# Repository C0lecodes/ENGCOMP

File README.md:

# PillPath — Dispenser Demonstration

PillPath is a local demonstration portal for the UC Engineering Challenge. It manages a small fleet of ESP32 pill dispensers, provides a care-team dashboard, maintains a dose history, alerts when a dose remains **undispensed** for 30 minutes, and alerts when medication stock reaches its refill threshold.

## Run the Portal

Requires Python 3.10+ and uses only the Python standard library.

From the project directory, run:

```sh
python3 server.py
```

Then open:

```text
http://localhost:3000
```

Press **Reset demo** to return to the initial demonstration data.

To demonstrate a missed-dose alert, add a dose with a scheduled time more than 30 minutes in the past.

## Demonstrate with an ESP32

### 1. Open the project

Open the project folder in VS Code and install the **PlatformIO IDE** extension if it is not already installed.

### 2. Configure the ESP32

Open:

```text
src/main.cpp
```

Set the Wi-Fi credentials for your network.

Then change `SERVER_URL` to the IP address of the computer running the PillPath server. For example:

```cpp
#define SERVER_URL "http://192.156.1.100:3000"
```

The computer and ESP32 must be connected to the same local network.

### 3. Connect and upload

Attach a momentary button between **GPIO 18** and **GND**.

In PlatformIO:

1. Select **Upload** to upload the firmware.
2. Select **Monitor** to open the serial monitor.
3. Press the button to trigger a demonstration dispense.

### 4. Demonstration mode

`DEMO_WITHOUT_MOTORS` is set to `true` by default.

This allows the ESP32 to be demonstrated without motor hardware connected. When the button is pressed, the ESP32:

1. Requests the next pending dose.
2. Simulates the dispensing cycle.
3. Records the dispense with the PillPath server.
4. Decreases the medication stock.

## Hardware Mapping and Safety

The PlatformIO firmware reserves the following GPIO pins for the motor drivers:

| GPIO    | Function               |
| ------- | ---------------------- |
| GPIO 26 | Top barrel step        |
| GPIO 27 | Top barrel direction   |
| GPIO 32 | Lower barrel step      |
| GPIO 33 | Lower barrel direction |

Set:

```cpp
DEMO_WITHOUT_MOTORS
```

to `false` only after the motor hardware has been connected and the `stepMotor` counts have been calibrated for the final mechanical gearing.

For a physical prototype, add appropriate end stops and/or jam detection before operating the mechanism unattended.

### Important limitation

PillPath records a **device dispensing action**. It does not verify that a person actually received or swallowed a medication.

This project is a demonstration prototype and must not be used for clinical decisions or real medication management without appropriate security, authentication, encrypted communication, audit controls, privacy review, and validated hardware and sensors.

## API Endpoints

### `POST /api/device/heartbeat`

Updates the connection status of an ESP32 dispenser.

### `POST /api/device/dispense`

Records a pending dose as dispensed and decreases the corresponding medication stock.

### `GET /api/dashboard`

Returns dashboard data and evaluates the current alerts.

## Data Storage

Persistent demonstration data is stored in:

```text
data.json
```

The file is created automatically when the server first saves data.

## Project Structure

A typical project structure is:

```text
PillPath/
├── server.py
├── data.json
├── src/
│   └── main.cpp
└── ...
```

`data.json` is generated automatically and does not need to be created manually.

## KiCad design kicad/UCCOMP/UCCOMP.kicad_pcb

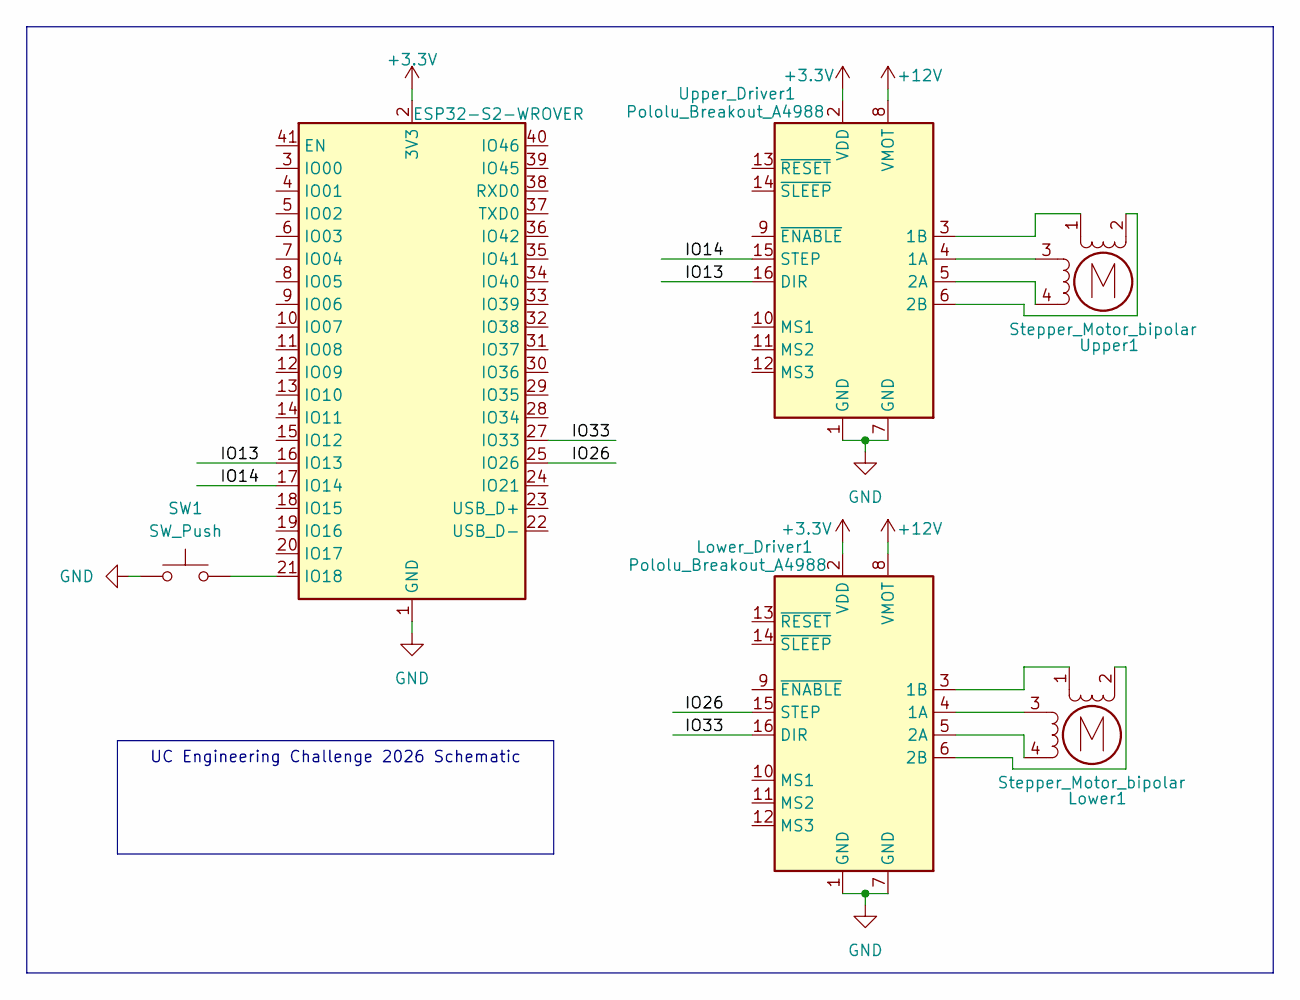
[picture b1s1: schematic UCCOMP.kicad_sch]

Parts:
Lower1: Stepper_Motor_bipolar; TerminalBlock_Phoenix_MKDS-1,5-4-5.08_1x04_P5.08mm_Horizont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
Lower_Driver1: Pololu_Breakout_A4988; Pololu_Breakout-16_15.2x20.3mm
SW1: SW_Push; SW_PUSH-12mm
U1: ESP32-S2-WROVER
Upper1: Stepper_Motor_bipolar; TerminalBlock_Phoenix_MKDS-1,5-4-5.08_1x04_P5.08mm_Horizont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
Upper_Driver1: Pololu_Breakout_A4988; Pololu_Breakout-16_15.2x20.3mm

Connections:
+3.3V: Lower_Driver1.2 (VDD), U1.2 (3V3), Upper_Driver1.2 (VDD)
+12V: Lower_Driver1.8 (VMOT), Upper_Driver1.8 (VMOT)
/IO13: U1.16 (IO13), Upper_Driver1.16 (DIR)
/IO14: U1.17 (IO14), Upper_Driver1.15 (STEP)
/IO26: Lower_Driver1.15 (STEP), U1.25 (IO26)
/IO33: Lower_Driver1.16 (DIR), U1.27 (IO33)
GND: Lower_Driver1.1 (GND), Lower_Driver1.7 (GND), SW1.1, U1.1 (GND), U1.26 (GND), U1.42 (GND), U1.43 (GND), Upper_Driver1.1 (GND), Upper_Driver1.7 (GND)
unnamed: Lower1.2 (-), Lower_Driver1.6 (2B)
unnamed: Lower1.3, Lower_Driver1.4 (1A)
unnamed: Lower1.1, Lower_Driver1.3 (1B)
unnamed: Lower1.4, Lower_Driver1.5 (2A)
unnamed: SW1.2, U1.21 (IO18)
unnamed: Upper1.2 (-), Upper_Driver1.6 (2B)
unnamed: Upper1.3, Upper_Driver1.4 (1A)
unnamed: Upper1.1, Upper_Driver1.3 (1B)
unnamed: Upper1.4, Upper_Driver1.5 (2A)

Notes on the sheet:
UC Engineering Challenge 2026 Schematic

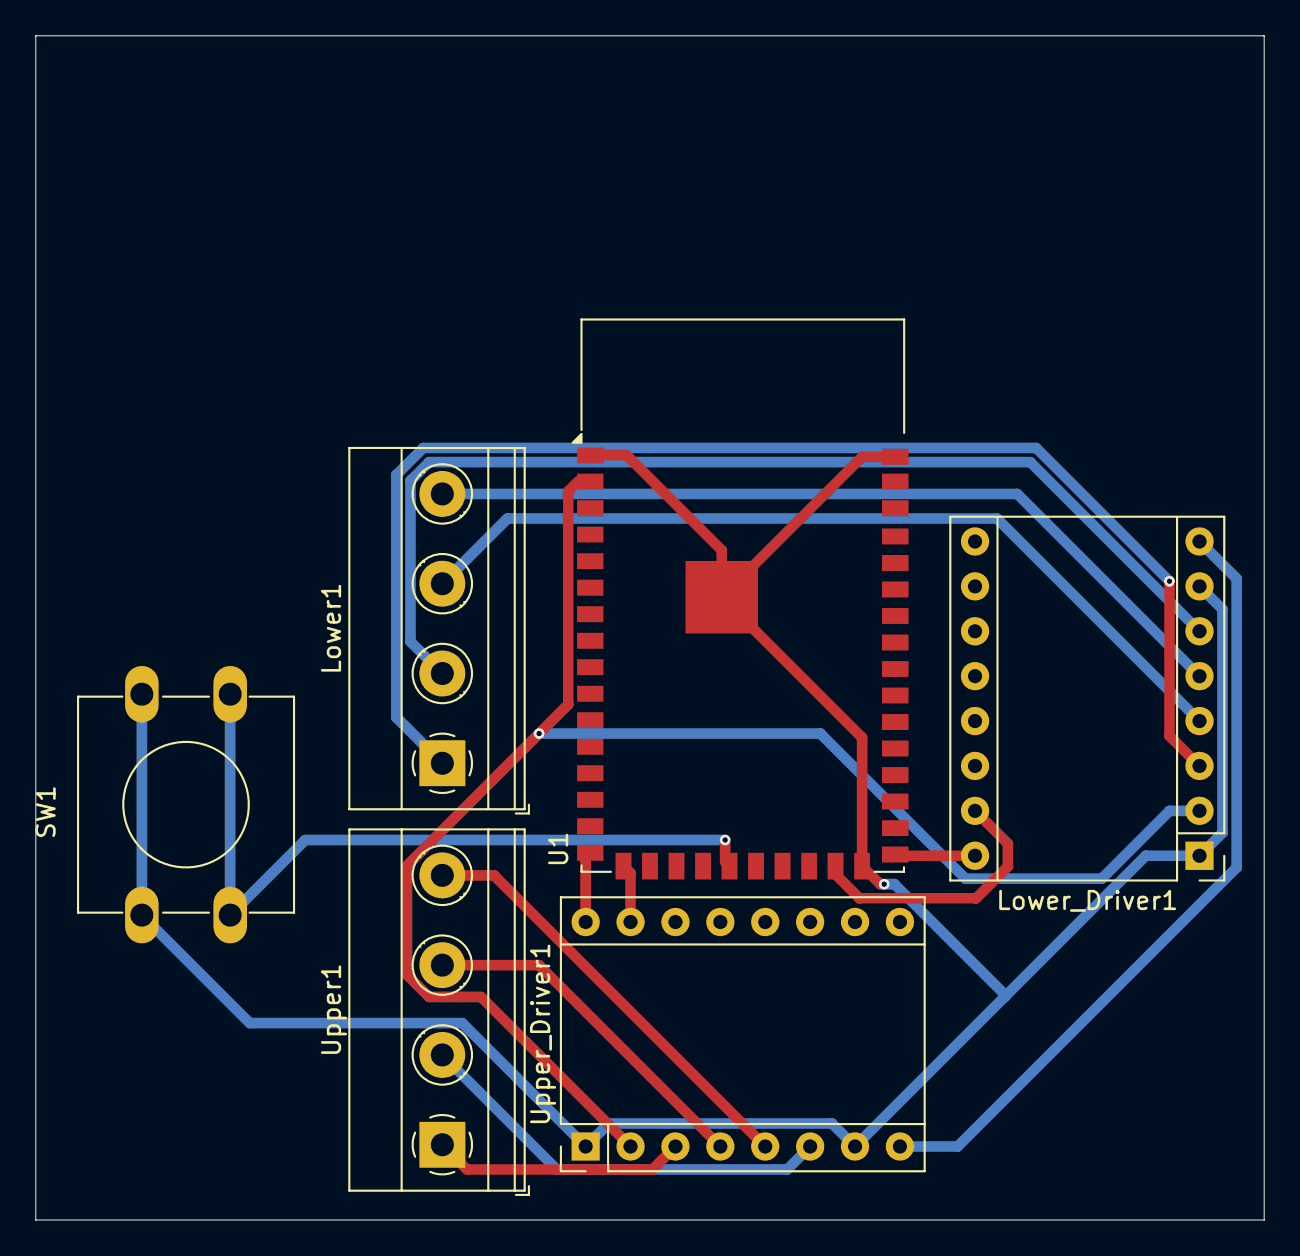
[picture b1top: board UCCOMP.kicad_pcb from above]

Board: 2 copper layers, 69.5 x 67.0 mm, 6 parts (0 on the bottom side), 16 nets.
